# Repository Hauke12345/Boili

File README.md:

# Boili

**A spot-price controller for electric water heaters.** An ESP32 fetches Nord Pool electricity prices over WiFi and switches the heater's contactor coil on during the cheapest hours. The tank's own thermostat and over-temperature limiter stay in series with the heater element.

This is a concept project designed together with Claude (Opus 5.5). It covers the circuit and PCB in KiCad, an injection-moulded enclosure in FreeCAD, renders and animations in Blender, and a mock-up sales page at **[boili.frenzyfront.io](https://boili.frenzyfront.io)**.

> **Status: design files only.** The circuit has been checked in SPICE simulation, but the board and enclosure have not been built or tested on real hardware, there is no firmware yet, and nothing here is certified (CE / LVD / EMC). It is a mains-voltage device: wiring must be done by a qualified electrician, and Boili only switches a contactor coil. It never carries the heater current itself.

## Contents

| Folder | What |
|---|---|
| [`hardware/pcb`](hardware/pcb) | KiCad 9 project (rev 1.0): schematic, 2-layer PCB, Gerbers, drill and pick-and-place files ready for a PCB fab, plus BOM, schematic PDF and 3D render. ERC and DRC are clean. See its README for the pinout, wiring and design choices. |
| [`hardware/pcb/simulation`](hardware/pcb/simulation) | ngspice checks of the relay driver, boot behaviour, supply rails under WiFi bursts, and power-up sequencing, with worst-case part values. All pass. One open point: the AMS1117 with ceramic output capacitors (see that README). |
| [`hardware/enclosure`](hardware/enclosure) | Two-part PC/ABS (V-0) injection-moulded enclosure with the BOILI logo embossed: STEP files for the toolmaker, the FreeCAD document, the parametric `housing.py` source and a fit/clearance report. Target IP54. |
| [`website`](website) | The mock-up sales page (`index.html` + `media/`). It illustrates Opus 5.5 capabilities and is not a real product listing. |
| [`media/videos`](media/videos) | Explainer animation, PCB design speedrun, enclosure modelling speedrun, and the combined film. |
| [`media/gifs`](media/gifs) | GIF versions for social media (each under 5 MB). |
| [`tools`](tools) | The scripts and Blender files that produced the media: explainer animation, PCB speedrun renderer, enclosure speedrun, studio product shots and turntable. |

## Hardware at a glance

- **Board:** 96.5 × 62 mm, 2 layers. Input is 230 VAC → T1A fuse → varistor → HLK-PM01 (isolated 5 V) → 3.3 V regulator → ESP32-WROOM module.
- **Output:** Omron G5Q-1A relay, which drives the coil of a separate contactor rated for the heater (e.g. 3-pole 25 A, AC-1).
- **Isolation:** at least 6 mm clearance and creepage between mains and low-voltage copper, enforced with a custom DRC rule.
- **Extras:** status LED, BOOT/boost button, optional DS18B20 temperature-sensor header, programming header for the first flash, then updates over WiFi.
- **Enclosure:** 133 × 95 × 33 mm, wall-mounted, 2 × M16 cable glands, tongue-and-groove gasket.

## Notes on the tools

The scripts in `tools/` ran in a sandbox (KiCad 9, Blender 5 with Cycles, FreeCAD 1.0). They use that sandbox's absolute paths (`/work/...`), so adjust the paths before re-running them. The explainer and render scripts expect the PCB and enclosure exports from `hardware/`.

## Still to do

- Firmware: price fetch, cheapest-hours scheduling, a fallback schedule when WiFi or prices are unavailable, a boost button, and updates over WiFi.
- A first prototype build, plus tests of the relay, power supply and thermal behaviour.
- Pre-compliance testing before any real-world use.

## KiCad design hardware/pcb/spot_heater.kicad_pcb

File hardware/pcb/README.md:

# Boili PCB: spot-price water heater controller (rev 1.0)

ESP32 board that turns a water heater's contactor on during the cheapest electricity hours.
It fetches Nord Pool spot prices over WiFi and switches the **contactor coil**, never the heater itself.
The tank's own thermostat and over-temperature limiter stay in series with the heater element.

KiCad 9 project. ERC: 0 errors / 0 warnings. DRC: 0 violations, 0 unconnected, schematic parity OK.
SPICE checks (relay driver, boot, supply rails, power-up) are in [`simulation/`](simulation).

## Files
| Path | What |
|---|---|
| `spot_heater.kicad_pro / .kicad_sch / .kicad_pcb` | The KiCad project |
| `spot_heater.kicad_dru` | Custom rule: 6 mm clearance **and** creepage between mains and low-voltage copper |
| `fab/` | Gerbers, drill file and pick-and-place file, ready to upload to a PCB fab |
| `docs/` | Schematic PDF, PCB top/bottom PDFs, 3D render, BOM (CSV) |

## Board
- 96.5 × 62 mm, 2 layers, 1.6 mm FR-4, 4 × M3 holes.
- Minimum drill 0.2 mm (the ESP32 module's ground-pad vias). Standard at most fabs, sometimes a small surcharge.
- Mains section on the left, low-voltage section on the right. A ground plane on the bottom layer covers only the low-voltage side.
- Mains tracks are 1.5 mm wide with 2 mm clearance between L and N.

## How it works
`J1` (230 VAC in) → `F1` T1A fuse → `RV1` varistor (surge protection) → `PS1` HLK-PM01 makes isolated 5 V → `U1` regulates to 3.3 V for the ESP32.
`IO26` drives `Q1`, which energises relay `K1`. `K1` connects fused L to `J2` and on to the contactor coil.
`R4` keeps the relay off while the ESP32 boots or resets.

| ESP32 pin | Function |
|---|---|
| IO26 | Heater enable (high = relay on) |
| IO25 | Status LED (green) |
| IO0 | BOOT button. After boot, use it as a manual "boost" button (active low) |
| IO4 | Optional DS18B20 on J4 (4.7 k pull-up fitted) |
| TXD0 / RXD0 | Programming header J3 |

## Wiring (by a qualified electrician)
- **J1:** L and N from a protected circuit.
- **J2:** to the contactor coil A1 (L_SW) and A2 (N). Use a 230 VAC coil contactor rated for the heater (e.g. 3-pole, 25 A, AC-1).
- Heater power goes through the contactor's main contacts and the tank thermostat/limiter, never through this board.
- K1 is rated far above a contactor coil's current. An RC snubber across the coil, often sold as an accessory for the contactor, reduces relay contact wear.
- Mount the board in a closed plastic enclosure.

## Programming
Connect a **3.3 V** USB-UART adapter to J3 (1=3V3, 2=GND, 3=TX, 4=RX, 5=EN, 6=IO0) **with mains disconnected**. Hold BOOT, tap RESET, then flash. After that, update over WiFi (OTA).

## Design choices
- **Relay:** Omron G5Q-1A. Its coil and contact pins sit at opposite ends of the relay, about 8 mm apart. On the G5LE the common contact sits between the coil pins.
- **Isolation:** the mains section and the HLK module's input are kept at least 6 mm from all low-voltage copper. This is checked by DRC, not just by eye.
- **Pins:** the relay and LED pins avoid the ESP32 strapping pins, so boot behaviour is unaffected.
- **Antenna:** the module antenna sits at the board edge with the footprint's copper keep-out respected.
- **Firmware fallback:** decide in firmware what happens without WiFi or prices. A fixed night schedule is suggested.

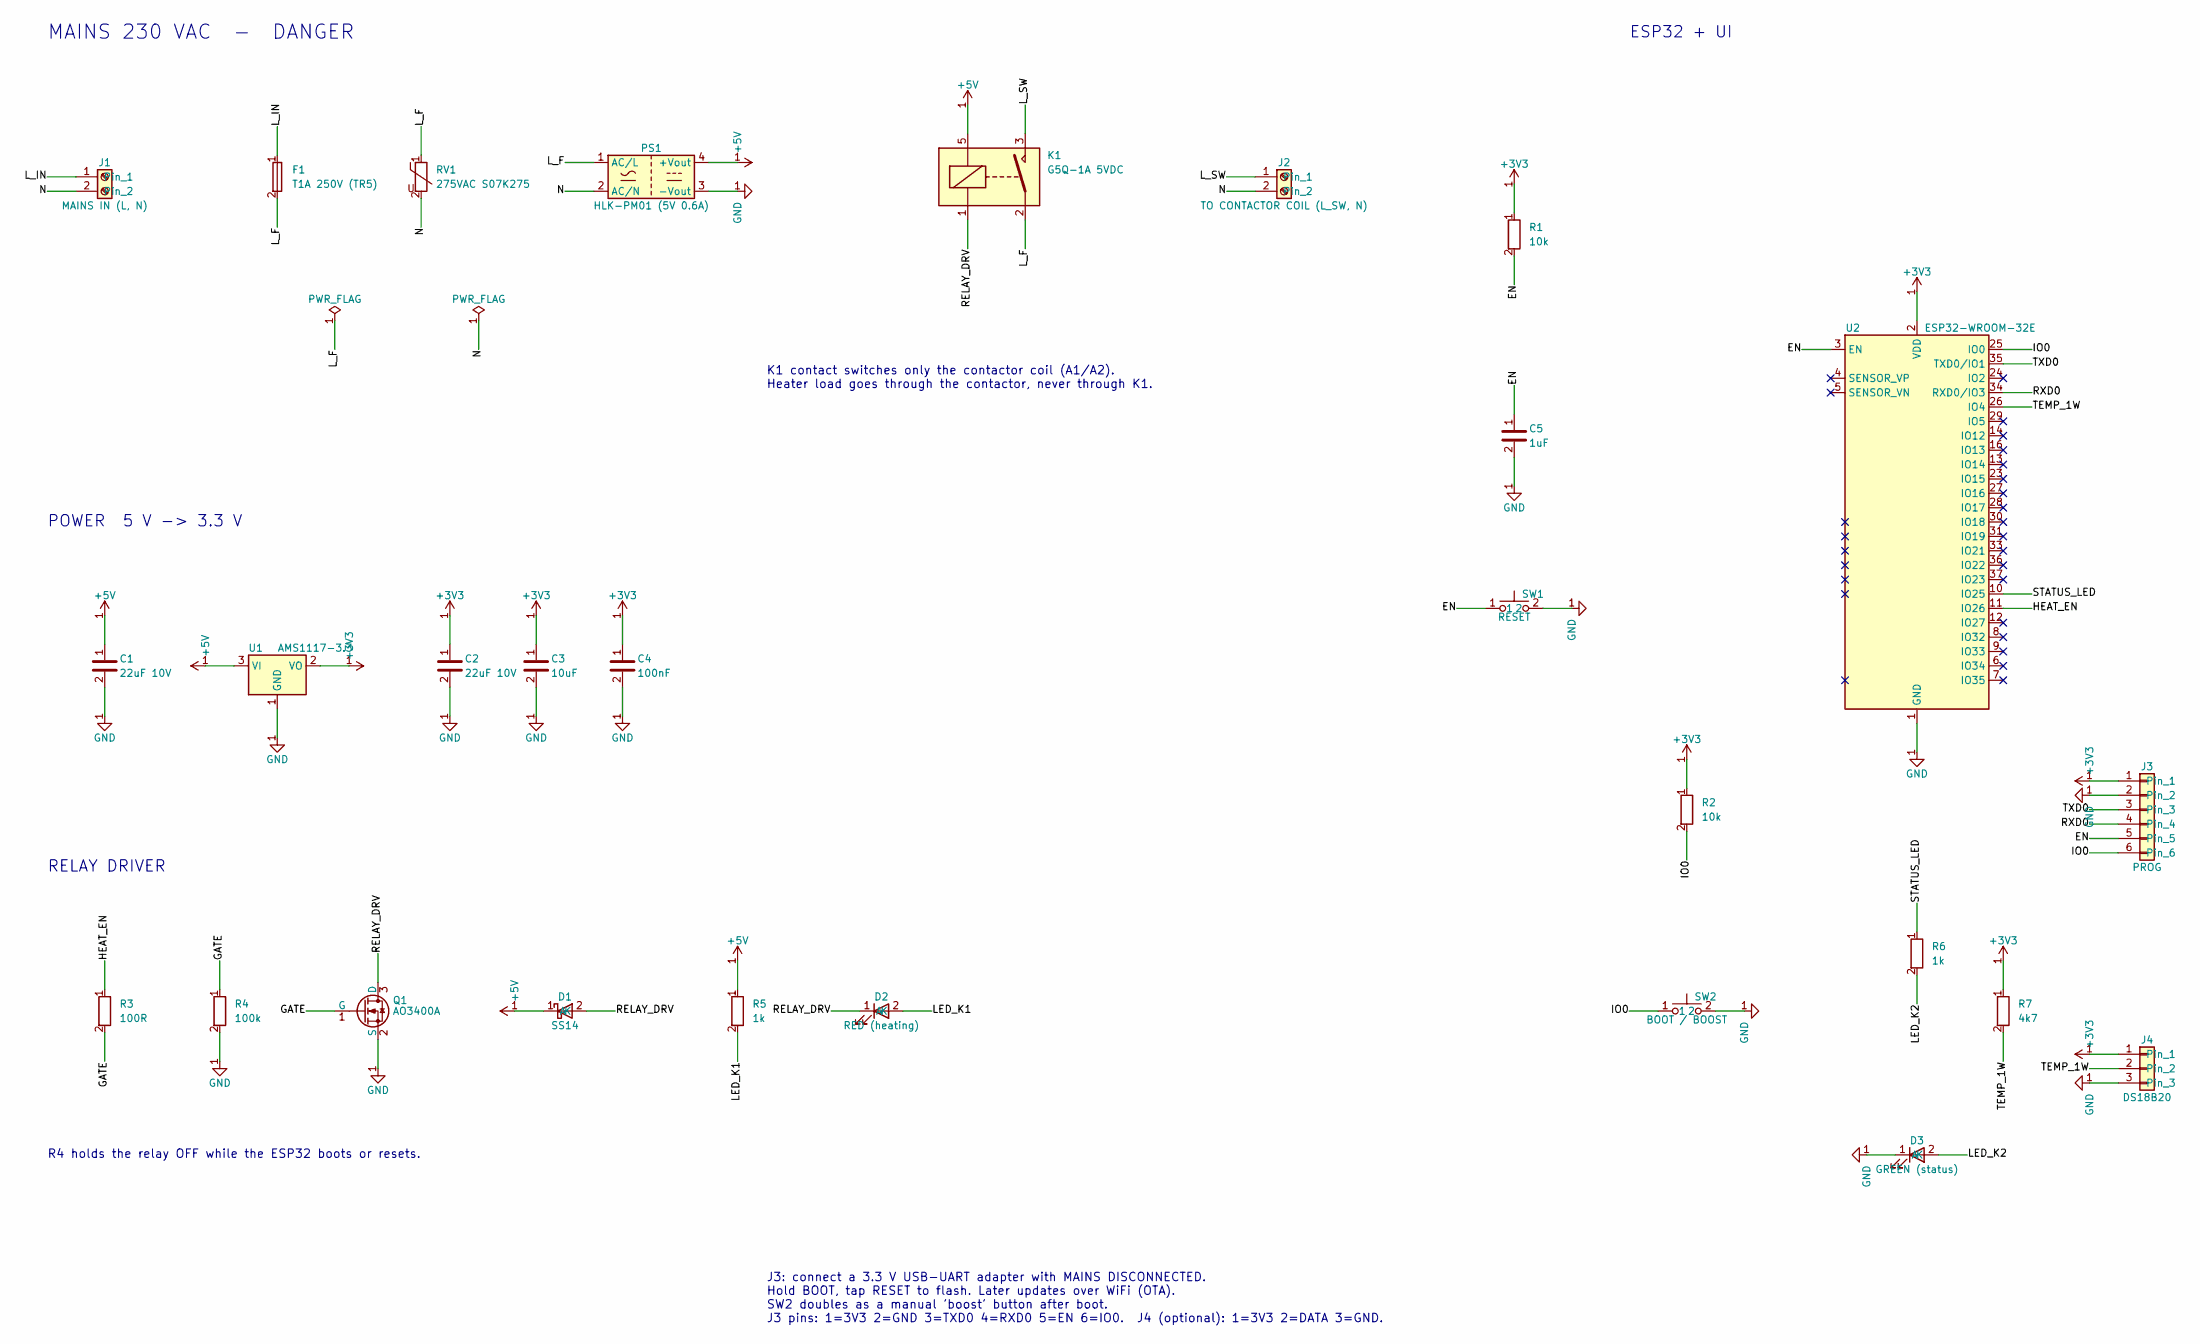
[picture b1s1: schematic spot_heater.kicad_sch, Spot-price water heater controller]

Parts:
C1, C2: 22uF 10V; C_1206_3216Metric
C3: 10uF; C_0805_2012Metric
C4: 100nF; C_0805_2012Metric
C5: 1uF; C_0805_2012Metric
D1: SS14; D_SMA
D2: RED (heating); LED_0805_2012Metric
D3: GREEN (status); LED_0805_2012Metric
F1: T1A 250V (TR5); Fuseholder_TR5_Littelfuse_No560_No460
J1: MAINS IN (L, N); TerminalBlock_Phoenix_MKDS-1,5-2-5.08_1x02_P5.08mm_Horizont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
J2: TO CONTACTOR COIL (L_SW, N); TerminalBlock_Phoenix_MKDS-1,5-2-5.08_1x02_P5.08mm_Horizont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
J3: PROG; PinHeader_1x06_P2.54mm_Vertical
J4: DS18B20; PinHeader_1x03_P2.54mm_Vertical
K1: G5Q-1A 5VDC; Relay_SPST_Omron-G5Q-1A
PS1: HLK-PM01 (5V 0.6A); Converter_ACDC_Hi-Link_HLK-PMxx
Q1: AO3400A; SOT-23
R1, R2: 10k; R_0805_2012Metric
R3: 100R; R_0805_2012Metric
R4: 100k; R_0805_2012Metric
R5, R6: 1k; R_0805_2012Metric
R7: 4k7; R_0805_2012Metric
RV1: 275VAC S07K275; RV_Disc_D7mm_W3.4mm_P5mm
SW1: RESET; SW_PUSH_6mm
SW2: BOOT / BOOST; SW_PUSH_6mm
U1: AMS1117-3.3; SOT-223-3_TabPin2
U2: ESP32-WROOM-32E; ESP32-WROOM-32

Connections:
+3V3: C2.1, C3.1, C4.1, J3.1, J4.1, R1.1, R2.1, R7.1, U1.2 (VO), U2.2 (VDD)
+5V: C1.1, D1.1 (K), K1.5, PS1.4 (+Vout), R5.1, U1.3 (VI)
/EN: C5.1, J3.5, R1.2, SW1.1, U2.3 (EN)
/GATE: Q1.1 (G), R3.2, R4.1
/HEAT_EN: R3.1, U2.11 (IO26)
/IO0: J3.6, R2.2, SW2.1, U2.25 (IO0)
/LED_K1: D2.2 (A), R5.2
/LED_K2: D3.2 (A), R6.2
/L_F: F1.2, K1.2, PS1.1 (AC/L), RV1.1
/L_IN: F1.1, J1.1
/L_SW: J2.1, K1.3
/N: J1.2, J2.2, PS1.2 (AC/N), RV1.2
/RELAY_DRV: D1.2 (A), D2.1 (K), K1.1, Q1.3 (D)
/RXD0: J3.4, U2.34 (RXD0/IO3)
/STATUS_LED: R6.1, U2.10 (IO25)
/TEMP_1W: J4.2, R7.2, U2.26 (IO4)
/TXD0: J3.3, U2.35 (TXD0/IO1)
GND: C1.2, C2.2, C3.2, C4.2, C5.2, D3.1 (K), J3.2, J4.3, PS1.3 (-Vout), Q1.2 (S), R4.2, SW1.2, SW2.2, U1.1 (GND), U2.1 (GND), U2.15 (GND), U2.38 (GND), U2.39 (GND)

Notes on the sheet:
MAINS 230 VAC - DANGER
K1 contact switches only the contactor coil (A1/A2). Heater load goes through the contactor, never through K1.
POWER 5 V -> 3.3 V
RELAY DRIVER
R4 holds the relay OFF while the ESP32 boots or resets.
ESP32 + UI
J3: connect a 3.3 V USB-UART adapter with MAINS DISCONNECTED. Hold BOOT, tap RESET to flash. Later updates over WiFi (OTA). SW2 doubles as a manual 'boost' button after boot. J3 pins: 1=3V3 2=GND 3=TXD0 4=RXD0 5=EN 6=IO0. J4 (optional): 1=3V3 2=DATA 3=GND.

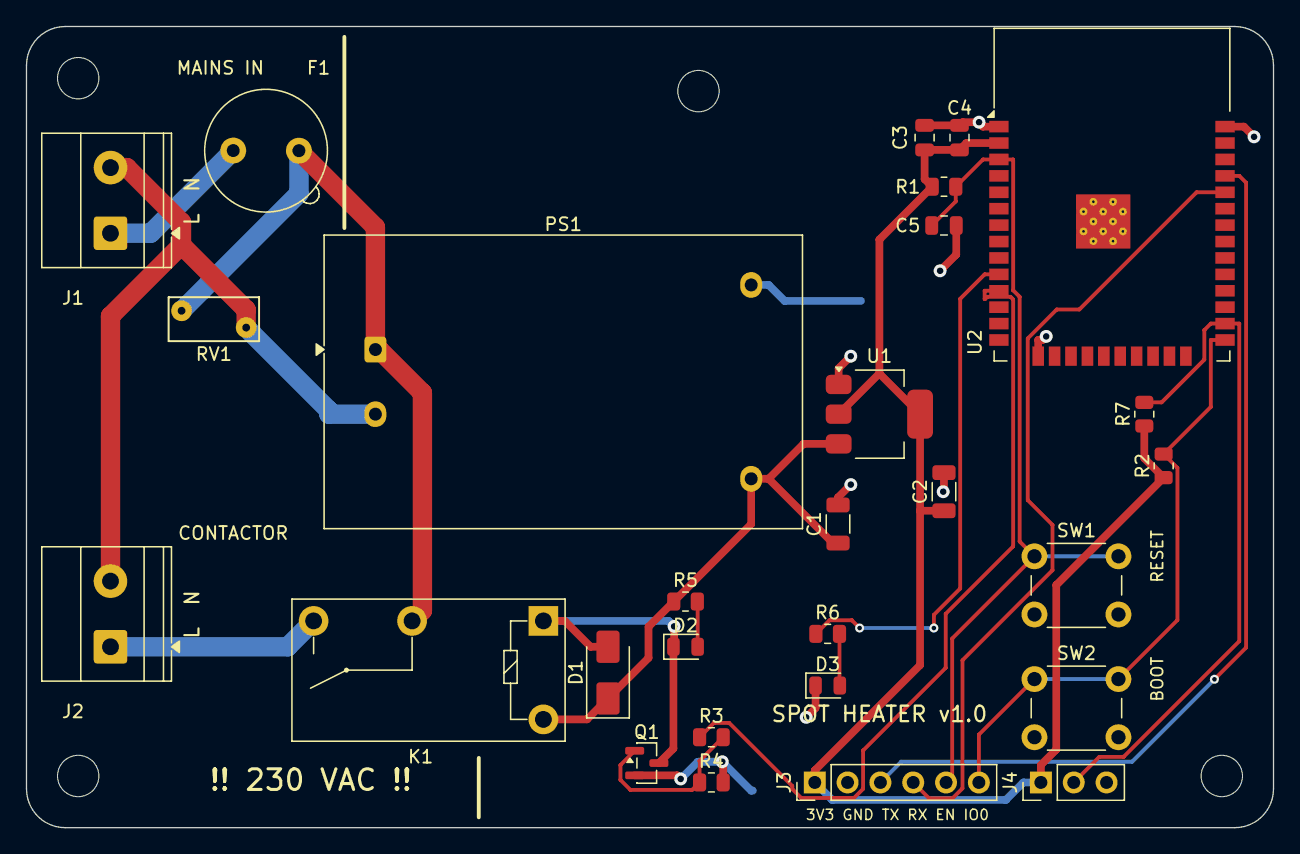
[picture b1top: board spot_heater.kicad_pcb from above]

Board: 2 copper layers, 96.5 x 62.0 mm, 32 parts (0 on the bottom side), 18 nets.

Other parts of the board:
H1, H2, H3, H4: M3; MountingHole_3.2mm_M3

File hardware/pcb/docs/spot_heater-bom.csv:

Qty,Refs,Value,Footprint
2,"C1,C2",22uF 10V,Capacitor_SMD:C_1206_3216Metric
1,C3,10uF,Capacitor_SMD:C_0805_2012Metric
1,C4,100nF,Capacitor_SMD:C_0805_2012Metric
1,C5,1uF,Capacitor_SMD:C_0805_2012Metric
1,D1,SS14,Diode_SMD:D_SMA
1,D2,RED (heating),LED_SMD:LED_0805_2012Metric
1,D3,GREEN (status),LED_SMD:LED_0805_2012Metric
1,F1,T1A 250V (TR5),Fuse:Fuseholder_TR5_Littelfuse_No560_No460
1,J1,"MAINS IN (L, N)","TerminalBlock_Phoenix:TerminalBlock_Phoenix_MKDS-1,5-2-5.08_1x02_P5.08mm_Horizontal"
1,J2,"TO CONTACTOR COIL (L_SW, N)","TerminalBlock_Phoenix:TerminalBlock_Phoenix_MKDS-1,5-2-5.08_1x02_P5.08mm_Horizontal"
1,J3,PROG,Connector_PinHeader_2.54mm:PinHeader_1x06_P2.54mm_Vertical
1,J4,DS18B20,Connector_PinHeader_2.54mm:PinHeader_1x03_P2.54mm_Vertical
1,K1,G5Q-1A 5VDC,Relay_THT:Relay_SPST_Omron-G5Q-1A
1,PS1,HLK-PM01 (5V 0.6A),Converter_ACDC:Converter_ACDC_Hi-Link_HLK-PMxx
1,Q1,AO3400A,Package_TO_SOT_SMD:SOT-23
2,"R1,R2",10k,Resistor_SMD:R_0805_2012Metric
1,R3,100R,Resistor_SMD:R_0805_2012Metric
1,R4,100k,Resistor_SMD:R_0805_2012Metric
2,"R5,R6",1k,Resistor_SMD:R_0805_2012Metric
1,R7,4k7,Resistor_SMD:R_0805_2012Metric
1,RV1,275VAC S07K275,Varistor:RV_Disc_D7mm_W3.4mm_P5mm
1,SW1,RESET,Button_Switch_THT:SW_PUSH_6mm
1,SW2,BOOT / BOOST,Button_Switch_THT:SW_PUSH_6mm
1,U1,AMS1117-3.3,Package_TO_SOT_SMD:SOT-223-3_TabPin2
1,U2,ESP32-WROOM-32E,RF_Module:ESP32-WROOM-32
